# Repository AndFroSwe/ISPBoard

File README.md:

# ISPBoard

This repo contains a project with a programming board for Atmel 28 DIP that can
be programmed using a 6-pin JTAG port (ISP). It is designed specifically for use
with ATmega 328P dip package.

# Software
For this project, the following software is used:

- KiCad
- Solid Edge

# Revisions

## Rev 1
External power needed. Test ports for leds, buttons and 2 pins from each pin
register.

## Rev 2
__Moved to this separate repo.__ 

Added battery power via a 9-5V DCDC converter. Improved layout. Added a port for
USART output. Added a 3D-printed case for the PCB.

# Future (potential) improvements

- USART output via FTDI chip to USB contact.

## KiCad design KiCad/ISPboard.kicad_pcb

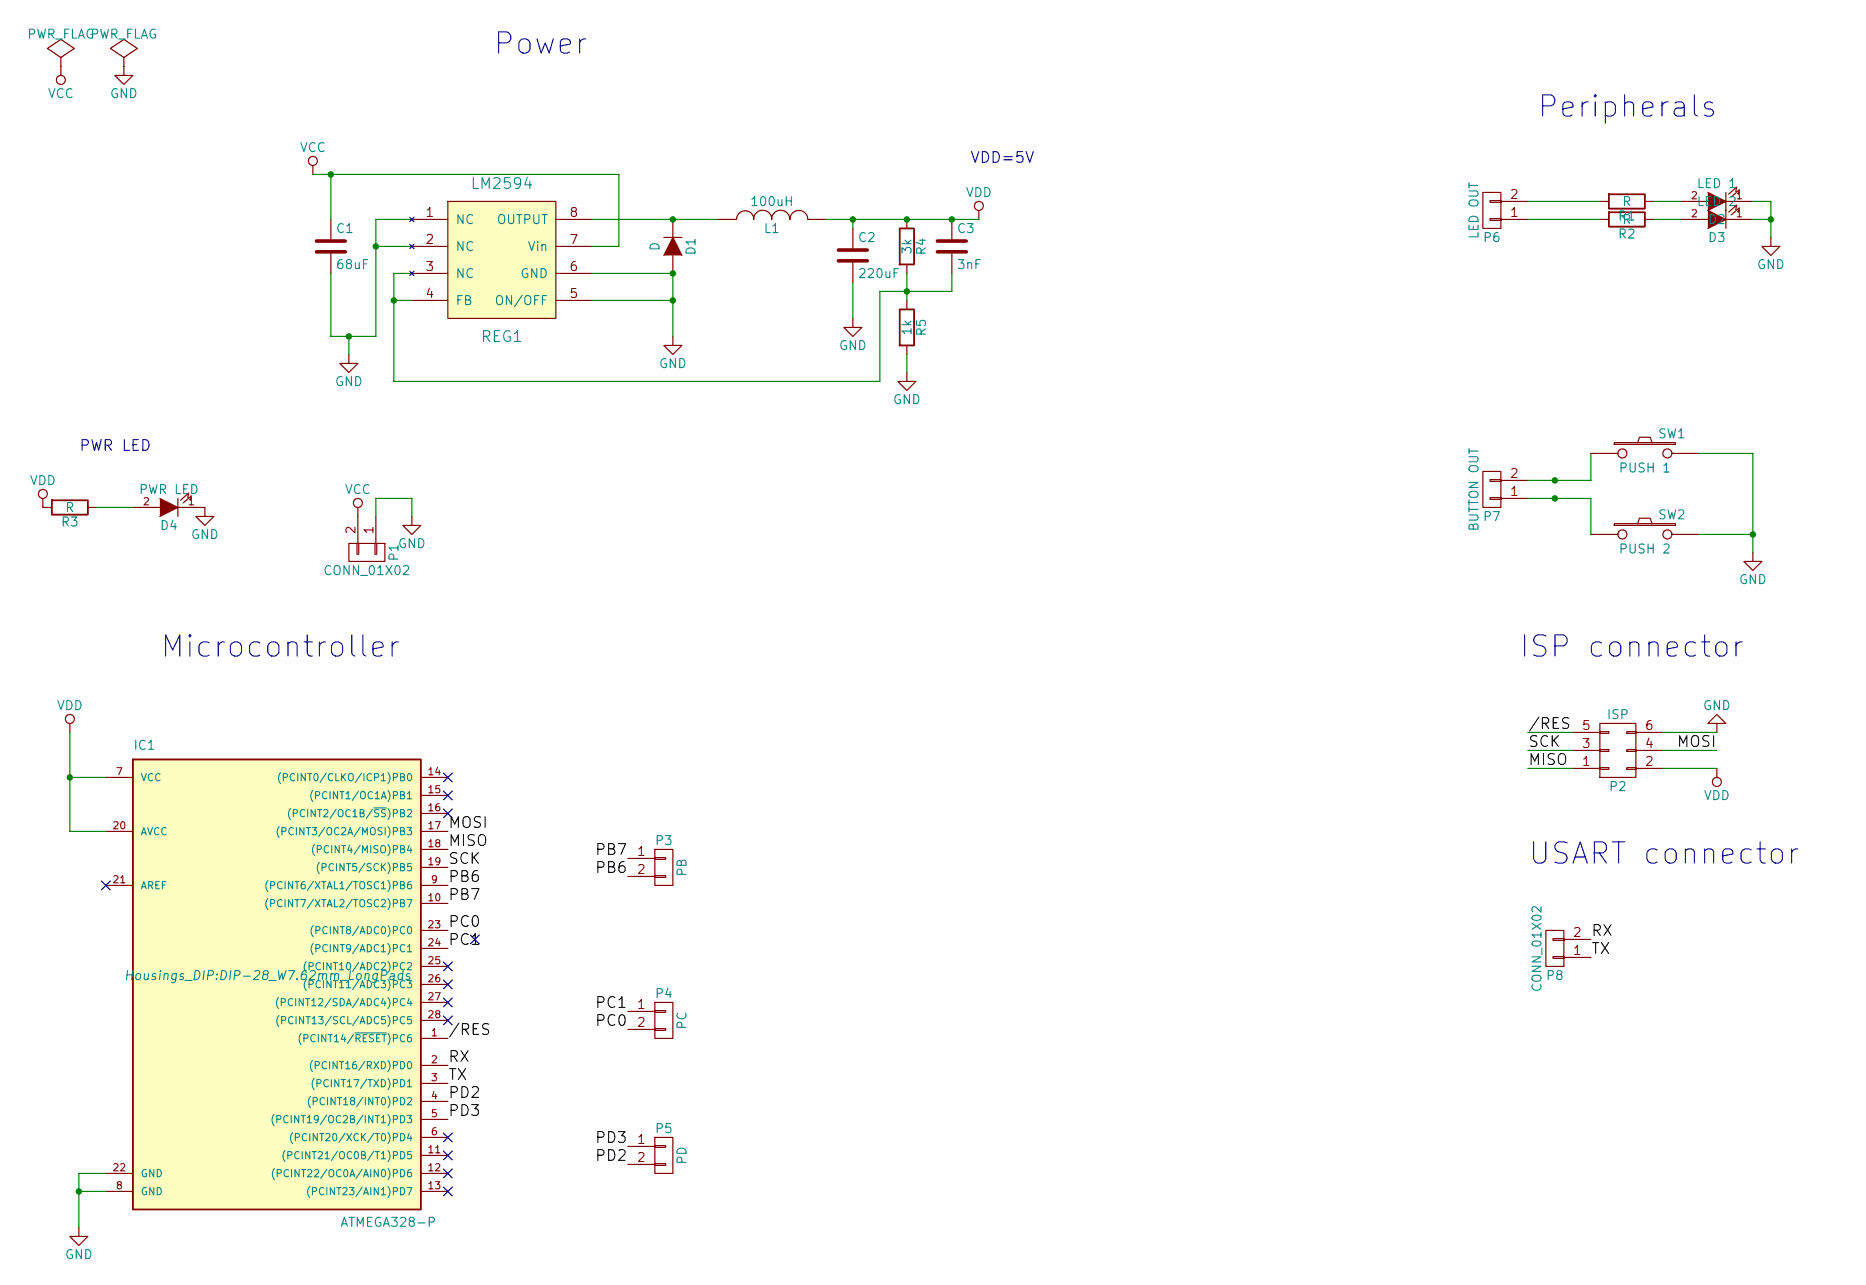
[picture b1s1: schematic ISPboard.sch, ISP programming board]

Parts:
C1: 68uF; c_elec_4x4.5
C2: 220uF; c_elec_4x4.5
C3: 3nF; C_0805_HandSoldering
D1: D; SMB_Handsoldering
D2: LED 1; LED-5MM
D3: LED 2; LED-5MM
D4: PWR LED; LED-5MM
IC1: ATMEGA328-P; DIP-28_W7.62mm_LongPads
L1: 100uH; Choke_SMD_Wuerth-WE-PD2-Typ-L
P1: CONN_01X02; Socket_Strip_Straight_1x02
P2: ISP; Socket_Strip_Straight_2x03
P3: PB; Molex_KK-6410-02_02x2.54mm_Straight
P4: PC; Molex_KK-6410-02_02x2.54mm_Straight
P5: PD; Molex_KK-6410-02_02x2.54mm_Straight
P6: LED OUT; Molex_KK-6410-02_02x2.54mm_Straight
P7: BUTTON OUT; Molex_KK-6410-02_02x2.54mm_Straight
P8: CONN_01X02; Molex_KK-6410-02_02x2.54mm_Straight
R1, R2, R3: R; R_1206_HandSoldering
R4: 3k; R_1206_HandSoldering
R5: 1k; R_1206_HandSoldering
REG1: LM2594; SOIC-8_3.9x4.9mm_Pitch1.27mm
SW1: PUSH 1; SW_PUSH_6mm
SW2: PUSH 2; SW_PUSH_6mm

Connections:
//RES: IC1.1 ((PCINT14/~RESET~)PC6), P2.5
/MISO: IC1.18 ((PCINT4/MISO)PB4), P2.1
/MOSI: IC1.17 ((PCINT3/OC2A/MOSI)PB3), P2.4
/PB6: IC1.9 ((PCINT6/XTAL1/TOSC1)PB6), P3.2
/PB7: IC1.10 ((PCINT7/XTAL2/TOSC2)PB7), P3.1
/PC0: IC1.23 ((PCINT8/ADC0)PC0), P4.2
/PC1: IC1.24 ((PCINT9/ADC1)PC1), P4.1
/PD2: IC1.4 ((PCINT18/INT0)PD2), P5.2
/PD3: IC1.5 ((PCINT19/OC2B/INT1)PD3), P5.1
/RX: IC1.2 ((PCINT16/RXD)PD0), P8.2
/SCK: IC1.19 ((PCINT5/SCK)PB5), P2.3
/TX: IC1.3 ((PCINT17/TXD)PD1), P8.1
GND: C1.2, C2.2, D1.2 (A), D2.1 (K), D3.1 (K), D4.1 (K), IC1.8 (GND), IC1.22 (GND), P1.1, P2.6, R5.2, REG1.1 (NC), REG1.2 (NC), REG1.5 (ON/OFF), REG1.6 (GND), SW1.2, SW2.2
unnamed: C3.2, R4.2, R5.1, REG1.3 (NC), REG1.4 (FB)
unnamed: D1.1 (K), L1.1, REG1.8 (OUTPUT)
unnamed: D2.2 (A), R1.1
unnamed: D3.2 (A), R2.1
unnamed: D4.2 (A), R3.1
unnamed: P6.1, R2.2
unnamed: P6.2, R1.2
unnamed: P7.1, SW2.1
unnamed: P7.2, SW1.1
VCC: C1.1, P1.2, REG1.7 (Vin)
VDD: C2.1, C3.1, IC1.7 (VCC), IC1.20 (AVCC), L1.2, P2.2, R3.2, R4.1

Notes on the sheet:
Microcontroller
Power
ISP connector
Peripherals
PWR LED
VDD=5V
USART connector

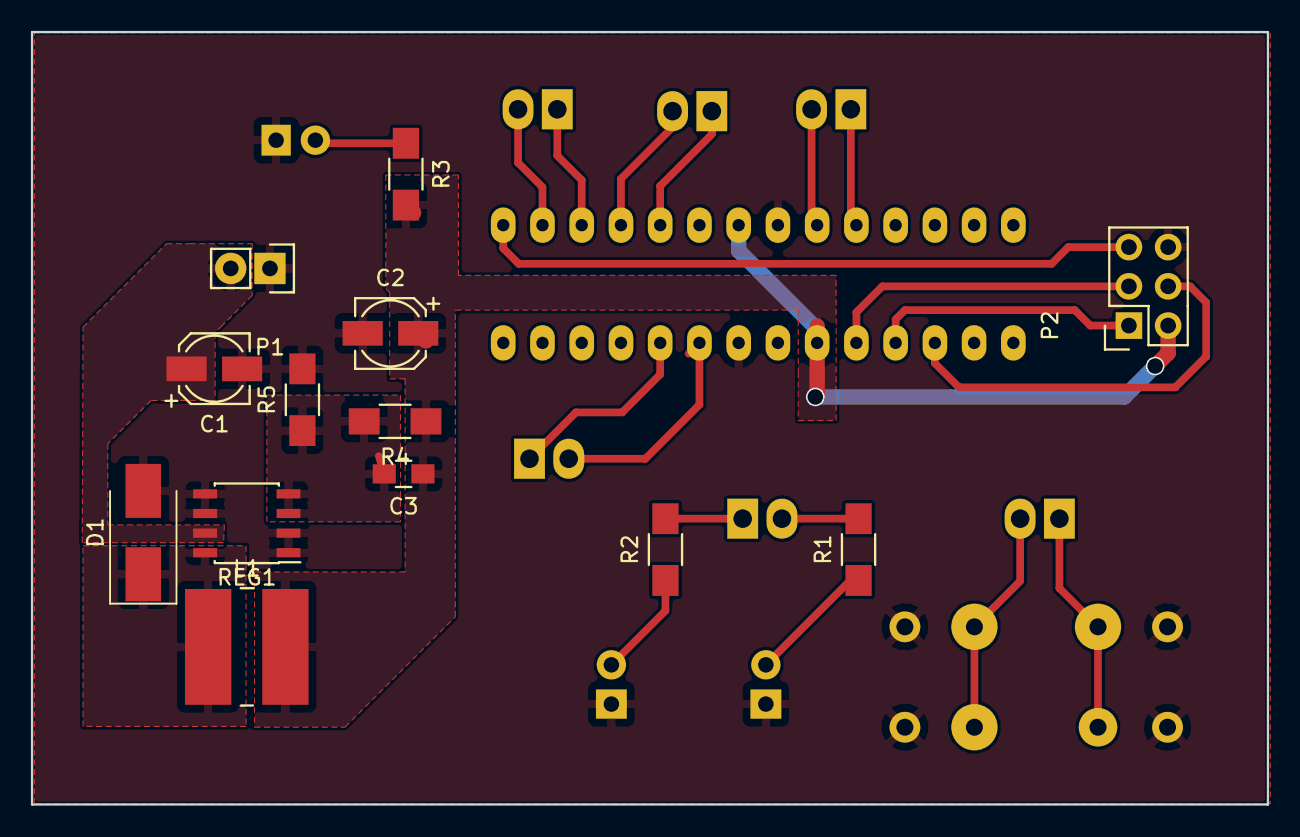
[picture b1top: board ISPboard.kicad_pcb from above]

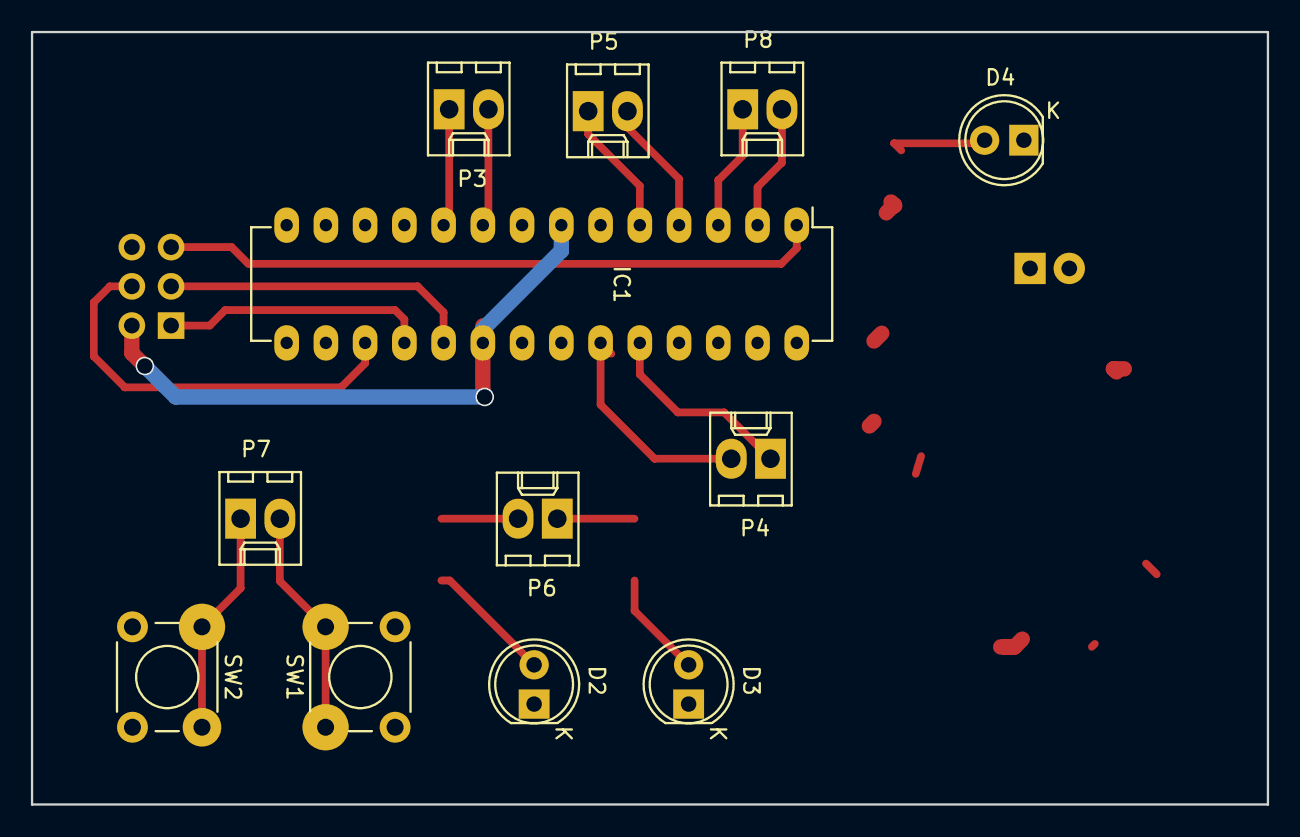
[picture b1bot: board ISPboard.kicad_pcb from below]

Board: 2 copper layers, 80.0 x 50.0 mm, 25 parts (12 on the bottom side), 24 nets.

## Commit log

2017-01-11 Initial commit to new repo. Made a proper README and moved all files to this repo
2017-01-13 Changed layout to have filled zones for input regulator
